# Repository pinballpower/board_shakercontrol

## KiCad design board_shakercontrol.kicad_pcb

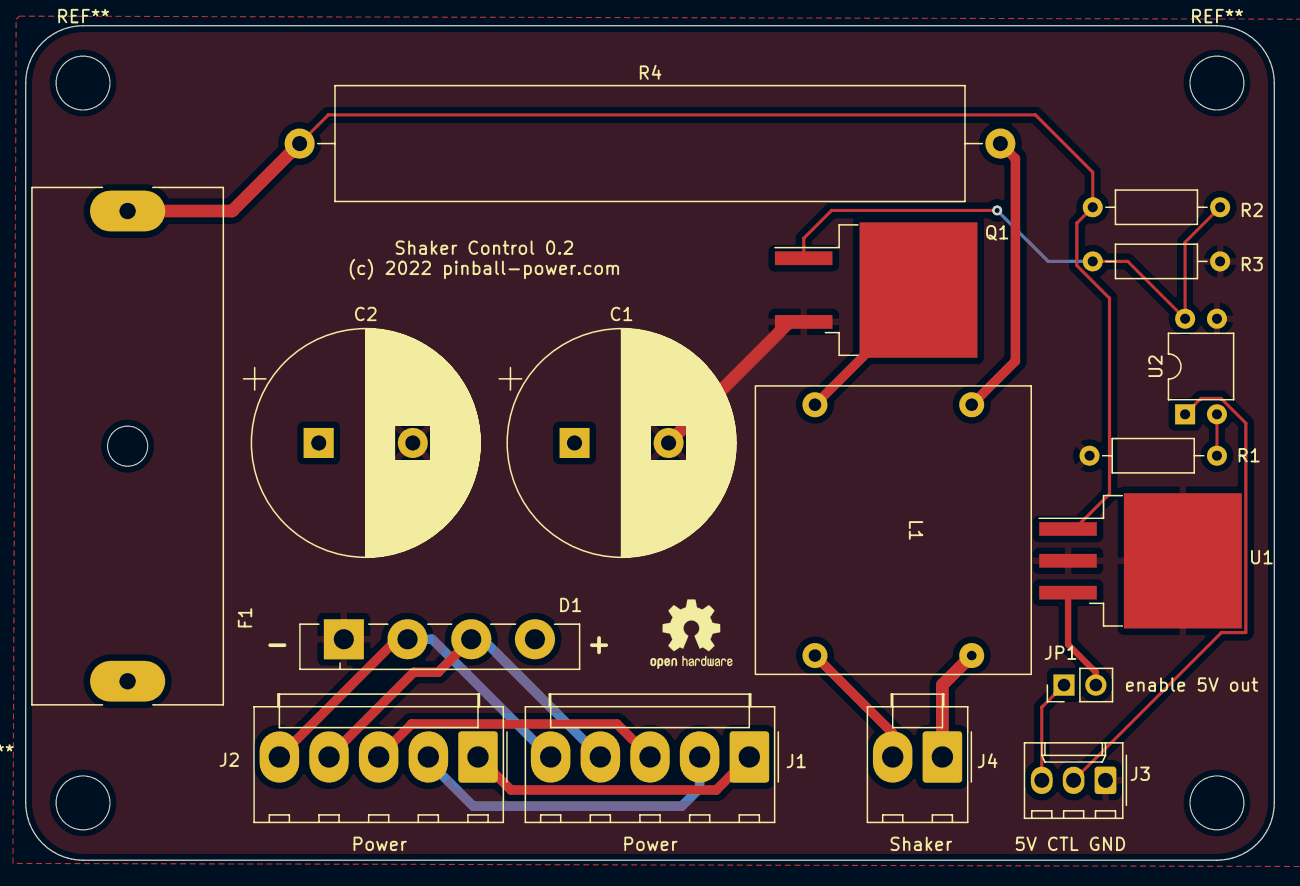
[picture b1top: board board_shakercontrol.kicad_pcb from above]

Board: 2 copper layers, 99.6 x 66.5 mm, 17 parts (0 on the bottom side), 17 nets.

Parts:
C1, C2: 3300u/35V; CP_Radial_D18.0mm_P7.50mm
D1: GBU8K; Diode_Bridge_Vishay_GBU
F1: 4A; Fuseholder_Cylinder-6.3x32mm_Schurter_0031-8002_Horizontal_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
J1, J2: Power; Molex_KK-396_A-41791-0005_1x05_P3.96mm_Vertical
J3: control / 5V; Molex_KK-254_AE-6410-03A_1x03_P2.54mm_Vertical
J4: Shaker; Molex_KK-396_A-41791-0002_1x02_P3.96mm_Vertical
JP1: enable 5V out; PinHeader_1x02_P2.54mm_Vertical
L1: CAF 3,1-1,2; CAF-12.5x20
Q1: IRF640NS; TO-263-2
R1: 100R; R_Axial_DIN0207_L6.3mm_D2.5mm_P10.16mm_Horizontal
R2, R3: 10k; R_Axial_DIN0207_L6.3mm_D2.5mm_P10.16mm_Horizontal
R4: 1R/11W; R_Axial_Power_L50.0mm_W9.0mm_P55.88mm
U1: L7805; TO-263-3_TabPin2
U2: LTV-817; DIP-4_W7.62mm

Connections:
+5V: JP1.2 (B), U1.3 (OUT)
/16VAC1: D1.3, J1.4, J2.4
/16VAC2: D1.2, J1.5, J2.5
/VIN: C1.1, C2.1, D1.4 (+), F1.1
GND: C1.2, C2.2, D1.1 (-), J3.1, Q1.3 (S), R1.1, R3.2, U1.2 (GND), U2.3
unnamed: J1.1, J2.1
unnamed: J1.2, J2.2
unnamed: J1.3, J2.3
unnamed: J3.2, U2.1
unnamed: J3.3, JP1.1 (A)
unnamed: J4.1, L1.4
unnamed: J4.2, L1.3
unnamed: L1.1, R4.2
unnamed: L1.2, Q1.2 (D)
unnamed: Q1.1 (G), R2.2, R3.1, U2.4
unnamed: R1.2, U2.2
VCC: F1.2, R2.1, R4.1, U1.1 (IN)

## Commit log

2022-01-30 Initial checkin
2022-01-30 First Gerber export
2022-01-30 Minor changes
2022-01-30 Changed control connection from 4 to 3 pin
2022-01-30 Slightly reduced board size

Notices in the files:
board_shakercontrol.kicad_pcb:
(c) 2022 pinball-power.com
